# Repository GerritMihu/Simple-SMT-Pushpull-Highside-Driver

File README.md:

# Simple-SMT-Pushpull-Highside-Driver
Mosfet-Highside-Drivercircuit

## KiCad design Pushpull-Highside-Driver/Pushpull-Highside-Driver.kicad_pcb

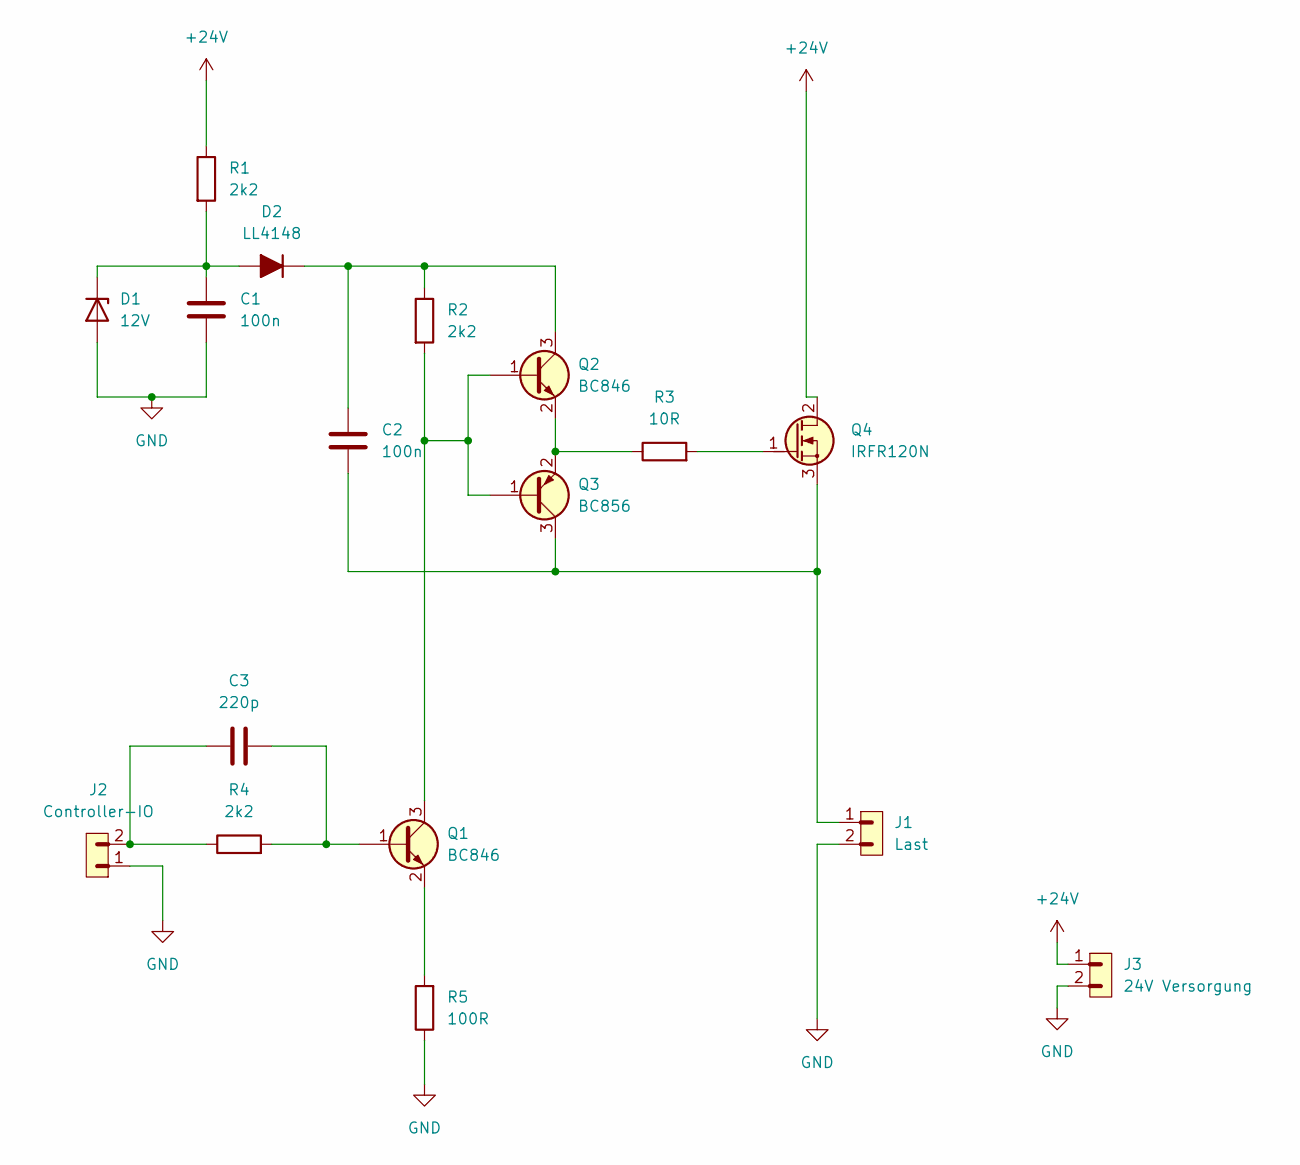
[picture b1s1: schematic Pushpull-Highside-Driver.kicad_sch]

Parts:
C1, C2: 100n; C_0805_2012Metric_Pad1.18x1.45mm_HandSolder
C3: 220p; C_0805_2012Metric_Pad1.18x1.45mm_HandSolder
D1: 12V; D_MiniMELF_Handsoldering
D2: LL4148; D_MiniMELF_Handsoldering
J1: Last; PinHeader_1x02_P2.54mm_Vertical
J2: Controller-IO; PinHeader_1x02_P2.54mm_Vertical
J3: 24V Versorgung; PinHeader_1x02_P2.54mm_Vertical
Q1, Q2: BC846; SOT-23
Q3: BC856; SOT-23
Q4: IRFR120N; TO-252-2
R1, R2, R4: 2k2; R_1206_3216Metric_Pad1.42x1.75mm_HandSolder
R3: 10R; R_1206_3216Metric_Pad1.42x1.75mm_HandSolder
R5: 100R; R_1206_3216Metric_Pad1.42x1.75mm_HandSolder

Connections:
+24V: J3.1, Q4.2 (D), R1.1
GND: C1.2, D1.2 (A), J1.2, J2.1, J3.2, R5.1
unnamed: C3.1, J2.2, R4.1
unnamed: C1.1, D1.1 (K), D2.2 (A), R1.2
unnamed: C2.1, D2.1 (K), Q2.3 (C), R2.1
unnamed: C3.2, Q1.1 (B), R4.2
unnamed: Q1.3 (C), Q2.1 (B), Q3.1 (B), R2.2
unnamed: Q1.2 (E), R5.2
unnamed: Q2.2 (E), Q3.2 (E), R3.1
unnamed: C2.2, J1.1, Q3.3 (C), Q4.3 (S)
unnamed: Q4.1 (G), R3.2

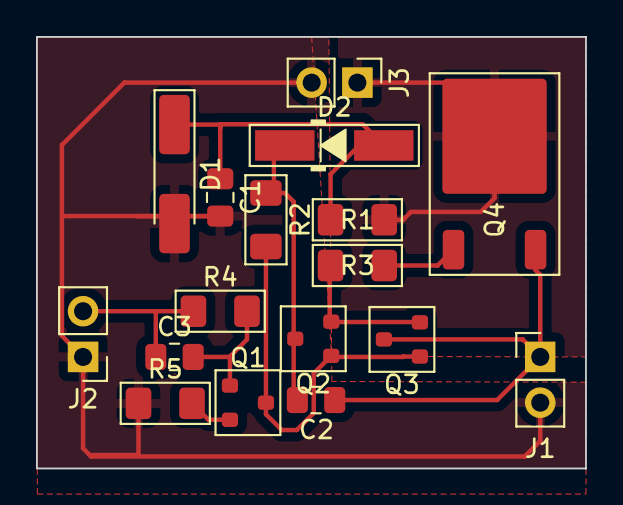
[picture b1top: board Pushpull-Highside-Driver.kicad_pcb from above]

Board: 2 copper layers, 30.5 x 24.0 mm, 17 parts (0 on the bottom side), 11 nets.

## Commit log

2024-01-20 Schaltplan
2024-01-20 Footprint
2024-01-21 PCB added
